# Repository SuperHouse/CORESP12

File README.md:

CoreSP12 ESP8266 Board
======================
Copyright 2015 SuperHouse Automation Pty Ltd <http://www.superhouse.tv>  

An ESP8266 module with the same footprint as a Spark Core or Particle
Photon, so that it can be a drop-in replacement for some projects.

Note: only a subset of the Core's I/O pins are connected, so this will
only work for projects that specifically use those pins. There are
many other limitations so use at your own risk!

More information is available at:

  http://www.superhouse.tv/coresp12

INSTALLATION
------------
The design is saved as an EAGLE project. EAGLE PCB design software is
available from www.cadsoftusa.com free for non-commercial use. To use
this project download it and place the directory containing these files
into the "eagle" directory on your computer. Then open EAGLE and
navigate to the project.

DISTRIBUTION
------------
The specific terms of distribution of this project are governed by the
license referenced below.

LICENSE
-------
Licensed under the TAPR Open Hardware License (www.tapr.org/OHL).
The "license" folder within this repository also contains a copy of
this license in plain text format.

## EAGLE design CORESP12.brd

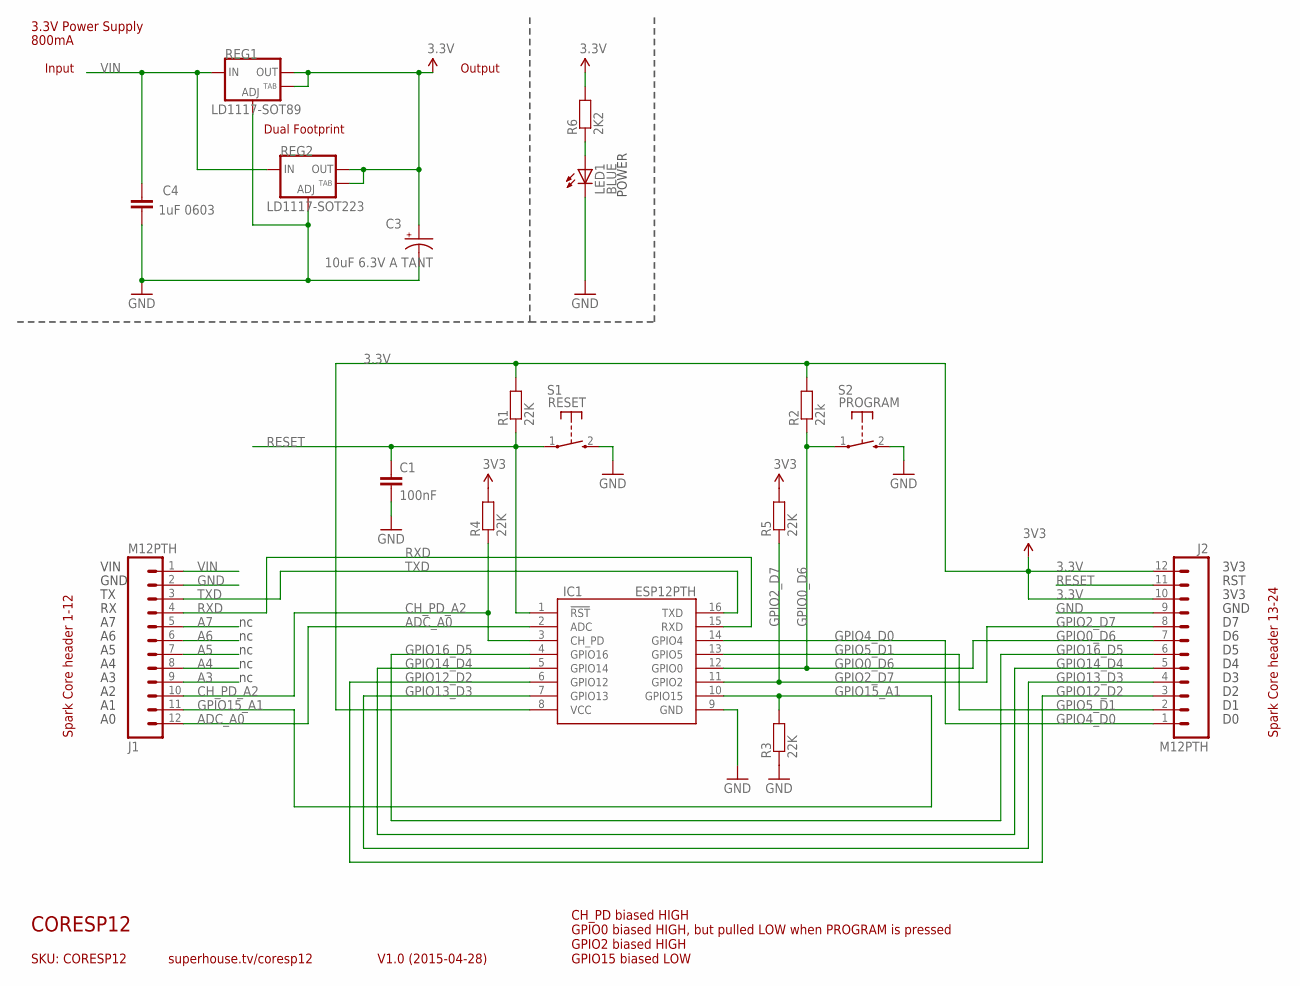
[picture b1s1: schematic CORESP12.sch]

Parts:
C1: 100nF; 0603
C3: 10uF 6.3V A TANT; EIA3216
C4: 1uF 0603; 0603
IC1: ESP12PTH
J1, J2: M12PTH; 1X12
LED1: BLUE; LED-0603
R1, R3, R4, R5: 22K; 0603
R2: 22k; 0603
R6: 2K2; 0603
REG1: LD1117-SOT89; SOT89
REG2: LD1117-SOT223; SOT223
S1: RESET; TACTILE_SWITCH_SMD_2PIN_TINY
S2: PROGRAM; TACTILE_SWITCH_SMD_2PIN_TINY

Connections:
3.3V: C3.A (+), IC1.8 (VCC), J2.10, J2.12, R1.2, R2.2, R4.2, R5.2, R6.2, REG1.2 (OUT), REG1.4 (OUT), REG2.2 (OUT), REG2.4 (OUT)
A3: J1.9
A4: J1.8
A5: J1.7
A6: J1.6
A7: J1.5
ADC_A0: IC1.2 (ADC), J1.12
CH_PD_A2: IC1.3 (CH_PD), J1.10, R4.1
GND: C1.2, C3.C (-), C4.2, IC1.9 (GND), J1.2, J2.9, LED1.C, R3.1, REG1.1 (ADJ), REG2.1 (ADJ), S1.2 (S), S2.2 (S)
GPIO0_D6: IC1.12 (GPIO0), J2.7, R2.1, S2.1
GPIO2_D7: IC1.11 (GPIO2), J2.8, R5.1
GPIO4_D0: IC1.14 (GPIO4), J2.1
GPIO5_D1: IC1.13 (GPIO5), J2.2
GPIO12_D2: IC1.6 (GPIO12), J2.3
GPIO13_D3: IC1.7 (GPIO13), J2.4
GPIO14_D4: IC1.5 (GPIO14), J2.5
GPIO15_A1: IC1.10 (GPIO15), J1.11, R3.2
GPIO16_D5: IC1.4 (GPIO16), J2.6
unnamed: LED1.A, R6.1
RESET: C1.1, IC1.1 (!RST), J2.11, R1.1, S1.1
RXD: IC1.15 (RXD), J1.4
TXD: IC1.16 (TXD), J1.3
VIN: C4.1, J1.1, REG1.3 (IN), REG2.3 (IN)

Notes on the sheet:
SKU: CORESP12
CORESP12
V1.0 (2015-04-28)
superhouse.tv/coresp12
CH_PD biased HIGH GPIO0 biased HIGH, but pulled LOW when PROGRAM is pressed GPIO2 biased HIGH GPIO15 biased LOW
3.3V Power Supply
Output
Input
POWER
Dual Footprint
800mA
Spark Core header 1-12
Spark Core header 13-24
VIN
GND
3V3
RST

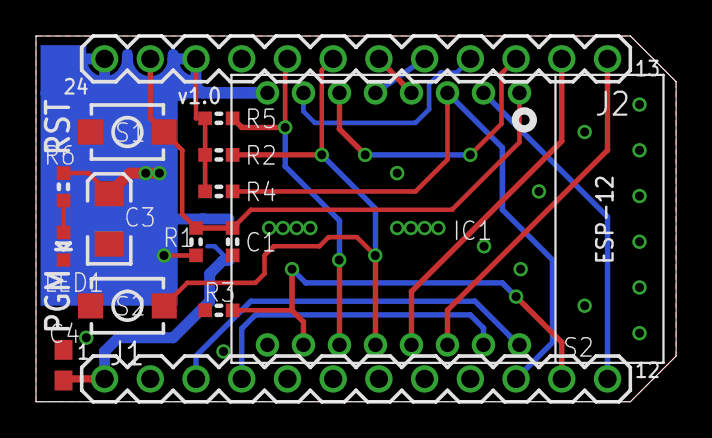
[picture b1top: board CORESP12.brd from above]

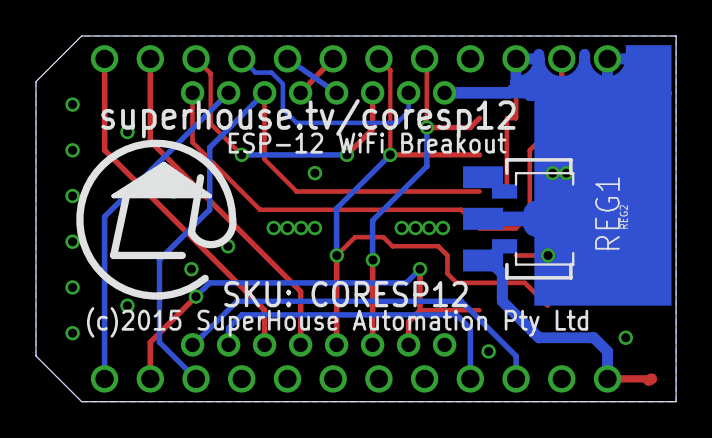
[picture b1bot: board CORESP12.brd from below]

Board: 2 copper layers, 35.6 x 20.3 mm, 17 parts (2 on the bottom side), 18 nets.

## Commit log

2018-03-27 Initial project import

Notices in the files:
CORESP12.brd:
(c)2015 SuperHouse Automation Pty Ltd
parts and their libraries:
freetronics-original: Licensing: CC v3.0 Share-Alike You are welcome to use this library for commercial purposes.
